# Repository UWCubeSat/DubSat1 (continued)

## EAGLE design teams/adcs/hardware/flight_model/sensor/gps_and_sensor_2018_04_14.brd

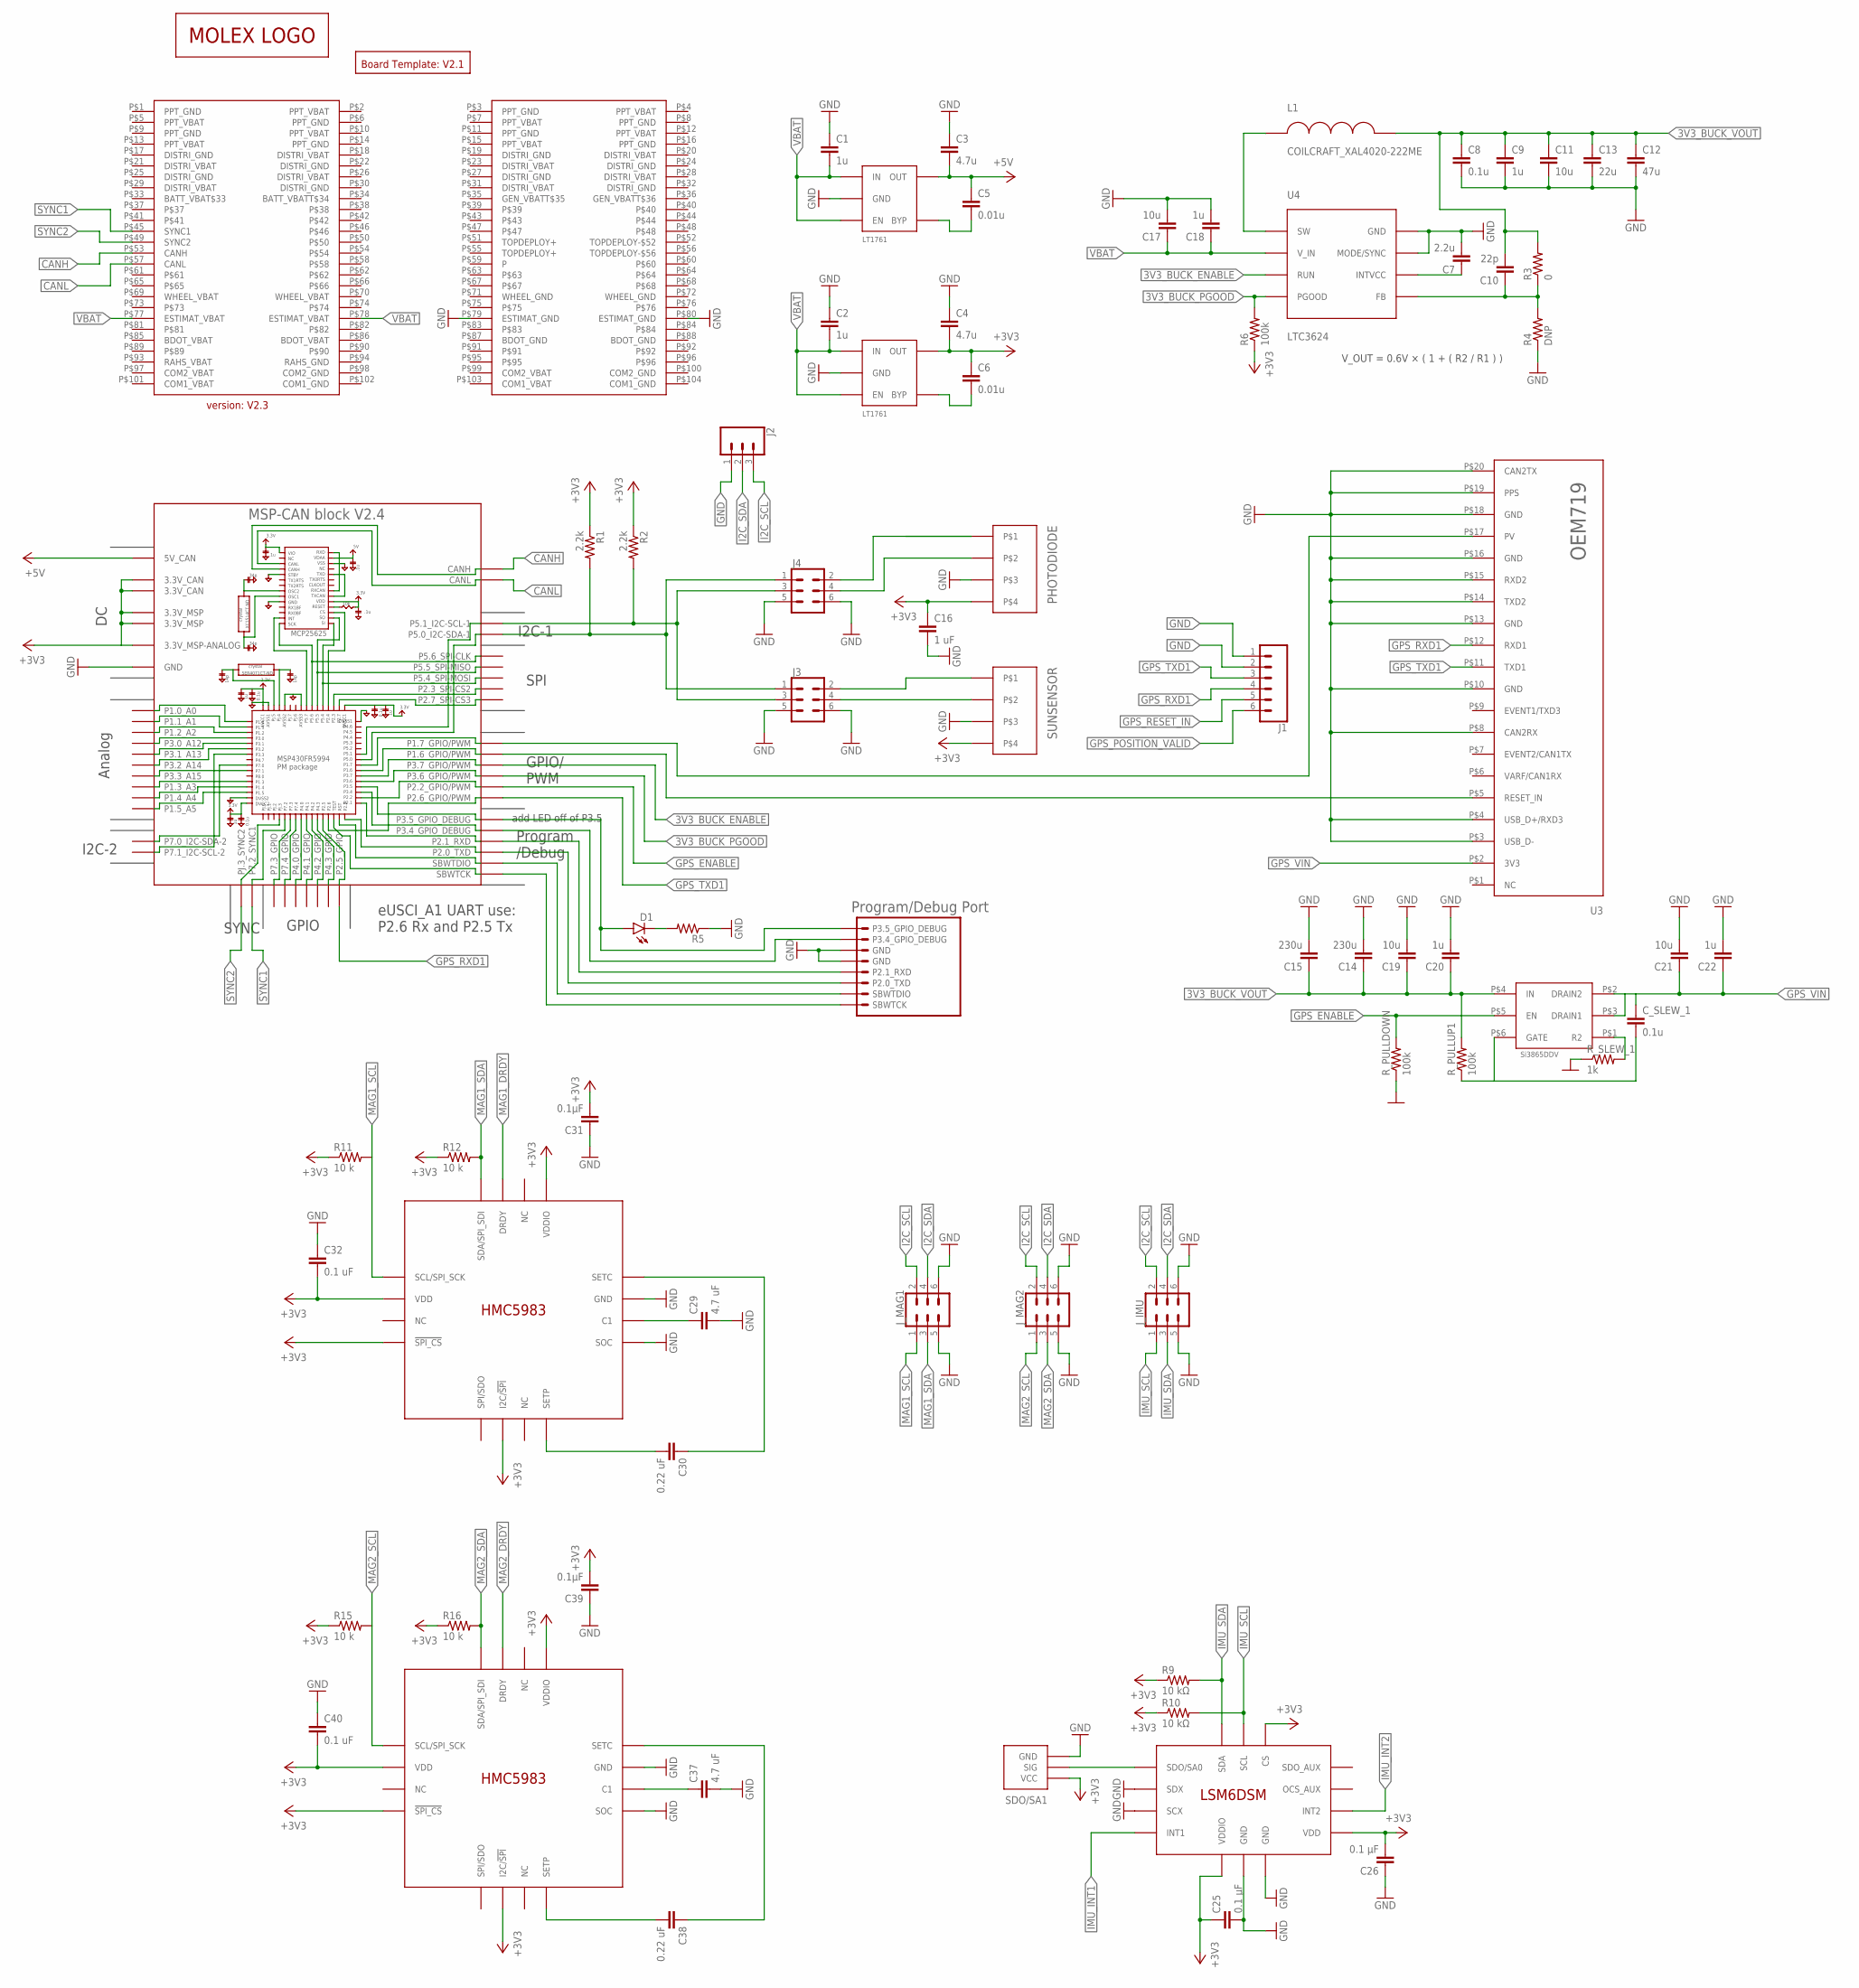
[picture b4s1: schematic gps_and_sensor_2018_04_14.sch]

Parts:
B1: BOARD_TEMPLATESERCURED; BOARD_TEMPLATE_SECURED
BLK1: MSP-CAN_BLOCK
C1, C2, C9, C18, C20, C22: 1u; 0805
C3, C4: 4.7u; 0805
C5, C6: 0.01u; 0805
C7: 2.2u; 0805
C8: 0.1u; 0805
C10: 22p; 0805
C11, C17, C19, C21: 10u; 0805
C12: 47u; 1206
C13: 22u; 1206
C14, C15: 230u; PANASONIC_SVPG
C16: 1 uF; 0805
C25, C26: 0.1 μF; 0805
C29, C37: 4.7 uF; 0805
C30, C38: 0.22 uF; 0805
C31, C39: 0.1µF; 0805
C32, C40: 0.1 uF; 0805
CONN1: PC104_CONNECTOR
C_SLEW_1: 0.1u; 0805
D1: LED; LED-1206
J1: CONN_06LOCK; 1X06_LOCK
J2: CONN_03LOCK; 1X03_LOCK
J3, J4: CONN_03X22X3_SILK_MALE_PTH; 2X3
J_IMU: CONN_03X22X3_SILK_MALE_PTH; 2X3
J_MAG1, J_MAG2: CONN_03X22X3_SILK_MALE_PTH; 2X3
L1: COILCRAFT_XAL4020-222ME; COILCRAFT_XAL4020
PHOTODIODE: PICOLOCK_4
R1, R2: 2.2k; 0805
R3: 0; 0805
R4: DNP; 0805
R5: RESISTOR0805; 0805
R6: 100k; 0805
R9, R10: 10 kΩ; 0805
R11, R12, R15, R16: 10 k; 0805
R_PULLDOWN: 100k; 0805
R_PULLUP1: 100k; 0805
R_SLEW_1: 1k; 0805
SDO/SA1: 0_OHM_JUMPER
SUNSENSOR: PICOLOCK_4
U1, U2: LT1761-X; SOT-23-5
U3: OEM719
U4: LTC3624
U$1: LOGO_MOLEX
U$2: PROGRAM/DEBUG_PORT; 1X08_CONNECTOR
U$3: SI3865DDV; TSOP-6
U$5: LSM6DSM
U$6, U$8: HMC5983

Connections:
3V3_BUCK_ENABLE: BLK1.P3.7_GPIO/PWM, U4.RUN
3V3_BUCK_FB: C10.1, R3.1, R4.2, U4.FB
3V3_BUCK_INTVCC: C7.1, U4.INTVCC
3V3_BUCK_PGOOD: BLK1.P3.6_GPIO/PWM, R6.2, U4.PGOOD
3V3_BUCK_SW: L1.P$1, U4.SW
3V3_BUCK_VOUT: C8.1, C9.1, C10.2, C11.1, C12.1, C13.1, C14.POS (1), C15.POS (1), C19.1, C20.1, L1.P$2, R3.2, R_PULLUP1.2, U$3.P$4 (IN)
+3V3: R6.1
CANH: BLK1.CANH, CONN1.P$53 (CANH)
CANL: BLK1.CANL, CONN1.P$57 (CANL)
GND: BLK1.GND@1 (GND), BLK1.GND@2 (GND), BLK1.GND@3 (GND), BLK1.GND@4 (GND), BLK1.GND@5 (GND), BLK1.GND@7 (GND), BLK1.GND@8 (GND), BLK1.GND@9 (GND), BLK1.GND@10 (GND), BLK1.GND@11 (GND), BLK1.GND@12 (GND), BLK1.GND@13 (GND), BLK1.GND@14 (GND), BLK1.GND@15 (GND), BLK1.GND@16 (GND), BLK1.GND@17 (GND), BLK1.GND@26 (GND), C1.1, C2.1, C3.1, C4.1, C7.2, C8.2, C9.2, C11.2, C12.2, C13.2, C14.NEG (2), C15.NEG (2), C16.2, C17.2, C18.2, C19.2, C20.2, C21.2, C22.2, C25.2, C26.1, C29.2, C31.1, C32.1, C37.2, C39.1, C40.1, CONN1.P$79 (ESTIMAT_GND), CONN1.P$80 (ESTIMAT_GND), J1.1, J1.2, J2.1, J3.5, J3.6, J4.5, J4.6, J_IMU.5, J_IMU.6, J_MAG1.5, J_MAG1.6, J_MAG2.5, J_MAG2.6, PHOTODIODE.P$3, R4.1, R5.1, R_PULLDOWN.1, R_SLEW_1.1, SDO/SA1.P$1 (GND), SUNSENSOR.P$3, U1.P$2 (GND), U2.P$2 (GND), U3.P$3 (USB_D-), U3.P$4 (USB_D+/RXD3), U3.P$8 (CAN2RX), U3.P$10 (GND), U3.P$13 (GND), U3.P$14 (TXD2), U3.P$15 (RXD2), U3.P$16 (GND), U3.P$18 (GND), U3.P$19 (PPS), U3.P$20 (CAN2TX), U4.GND@1 (GND), U4.GND@PAD (GND), U4.MODE/SYNC, U$2.5 (GND), U$2.6 (GND), U$5.GND@1 (GND), U$5.GND@2 (GND), U$5.SCX, U$5.SDX, U$6.GND, U$6.SOC, U$8.GND, U$8.SOC
GPS_ENABLE: BLK1.P2.2_GPIO/PWM, R_PULLDOWN.2, U$3.P$5 (EN)
GPS_POSITION_VALID: BLK1.P1.7_GPIO/PWM, J1.6, U3.P$17 (PV)
GPS_RESET_IN: BLK1.P1.6_GPIO/PWM, J1.5, U3.P$5 (RESET_IN)
GPS_RXD1: BLK1.P2.5_GPIO, J1.4, U3.P$12 (RXD1)
GPS_TXD1: BLK1.P2.6_GPIO/PWM, J1.3, U3.P$11 (TXD1)
GPS_VIN: C21.1, C22.1, C_SLEW_1.1, U3.P$2 (3V3), U$3.P$2 (DRAIN2), U$3.P$3 (DRAIN1)
I2C_SCL: BLK1.P5.1_I2C-SCL-1, J2.3, J3.3, J4.3, J_IMU.2, J_MAG1.2, J_MAG2.2, R2.2
I2C_SDA: BLK1.P5.0_I2C-SDA-1, J2.2, J3.1, J4.1, J_IMU.4, J_MAG1.4, J_MAG2.4, R1.2
IMU_INT1: U$5.INT1
IMU_INT2: U$5.INT2
IMU_SCL: J_IMU.1, R10.2, U$5.SCL
IMU_SDA: J_IMU.3, R9.2, U$5.SDA
LDO_3V3: BLK1.3.3V@CAN1 (3.3V_CAN), BLK1.3.3V@CAN2 (3.3V_CAN), BLK1.3.3V@MSP1 (3.3V_MSP), BLK1.3.3V@MSP2 (3.3V_MSP), BLK1.3.3V_ANALOG@MSP2 (3.3V_MSP-ANALOG), C4.2, C6.1, C16.1, C25.1, C26.2, C31.2, C32.2, C39.2, C40.2, PHOTODIODE.P$4, R1.1, R2.1, R9.1, R10.1, R11.1, R12.1, R15.1, R16.1, SDO/SA1.P$3 (VCC), SUNSENSOR.P$4, U2.P$5 (OUT), U$5.CS, U$5.VDD, U$5.VDDIO, U$6.!SPI_CS, U$6.I2C/!SPI, U$6.VDD, U$6.VDDIO, U$8.!SPI_CS, U$8.I2C/!SPI, U$8.VDD, U$8.VDDIO
LDO_3V3_BYP: C6.2, U2.P$4 (BYP)
LDO_5V: BLK1.5V (5V_CAN), C3.2, C5.1, U1.P$5 (OUT)
LDO_5V_BYP: C5.2, U1.P$4 (BYP)
MA1G_C2: C29.1, U$6.C1
MAG1_DRDY: U$6.DRDY
MAG1_SCL: J_MAG1.1, R11.2, U$6.SCL/SPI_SCK
MAG1_SDA: J_MAG1.3, R12.2, U$6.SDA/SPI_SDI
MAG1_SETC1: C30.1, U$6.SETC
MAG1_SETP1: C30.2, U$6.SETP
MAG2_C1: C37.1, U$8.C1
MAG2_DRDY: U$8.DRDY
MAG2_SCL: J_MAG2.1, R15.2, U$8.SCL/SPI_SCK
MAG2_SDA: J_MAG2.3, R16.2, U$8.SDA/SPI_SDI
MAG2_SETC: C38.1, U$8.SETC
MAG2_SETP: C38.2, U$8.SETP
unnamed: BLK1.P3.5_GPIO_DEBUG, D1.A, U$2.8 (P3.5_GPIO_DEBUG)
unnamed: R_SLEW_1.2, U$3.P$1 (R2)
unnamed: BLK1.P3.4_GPIO_DEBUG, U$2.7 (P3.4_GPIO_DEBUG)
unnamed: C_SLEW_1.2, R_PULLUP1.1, U$3.P$6 (GATE)
unnamed: BLK1.P2.1_RXD, U$2.4 (P2.1_RXD)
unnamed: BLK1.P2.0_TXD, U$2.3 (P2.0_TXD)
unnamed: BLK1.SBWTDIO, U$2.2 (SBWTDIO)
unnamed: BLK1.SBWTCK, U$2.SBWTCK
unnamed: D1.C, R5.2
unnamed: SDO/SA1.P$2 (SIG), U$5.SDO/SA0
PHOTODIODE_SCL: J4.4, PHOTODIODE.P$2
PHOTODIODE_SDA: J4.2, PHOTODIODE.P$1
SUNSENSOR_SCL: J3.4, SUNSENSOR.P$2
SUNSENSOR_SDA: J3.2, SUNSENSOR.P$1
SYNC1: BLK1.P7.2_SYNC1, CONN1.P$45 (SYNC1)
SYNC2: BLK1.PJ.3_SYNC2, CONN1.P$49 (SYNC2)
VBAT: C1.2, C2.2, C17.1, C18.1, CONN1.P$77 (ESTIMAT_VBAT), CONN1.P$78 (ESTIMAT_VBAT), U1.P$1 (IN), U1.P$3 (EN), U2.P$1 (IN), U2.P$3 (EN), U4.V_IN

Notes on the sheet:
V_OUT = 0.6V × ( 1 + ( R2 / R1 ) )

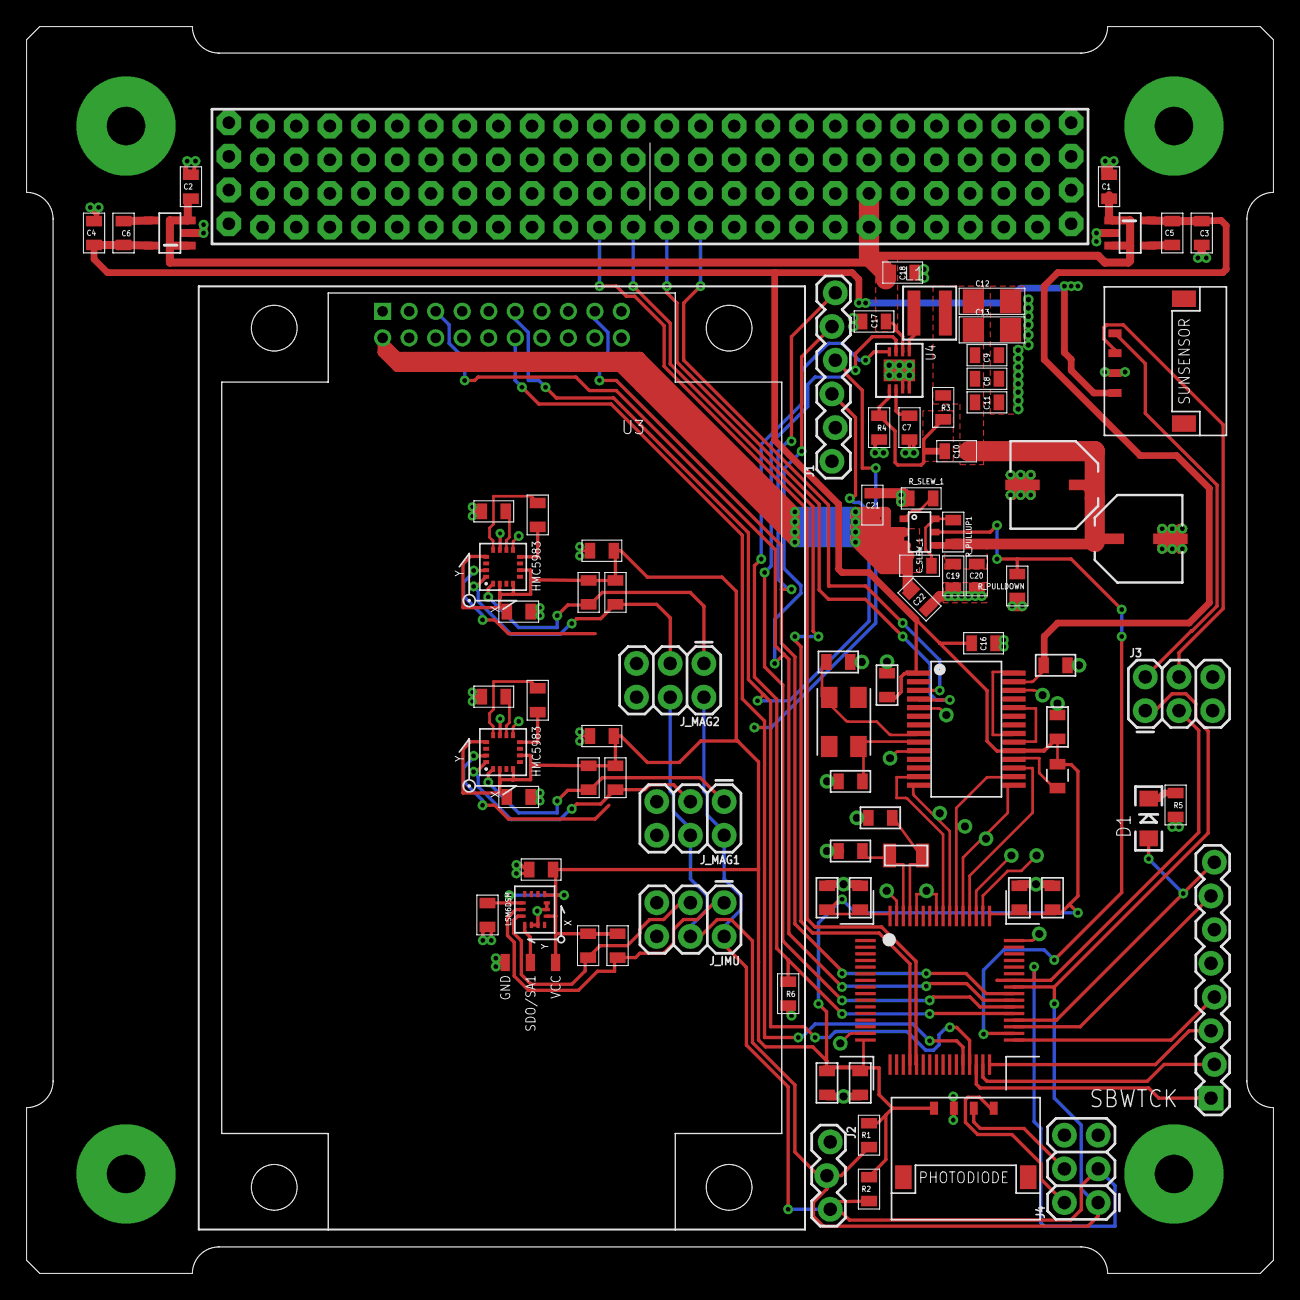
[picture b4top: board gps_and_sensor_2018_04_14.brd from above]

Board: 2 copper layers, 94.0 x 94.0 mm, 73 parts (1 on the bottom side), 50 nets.

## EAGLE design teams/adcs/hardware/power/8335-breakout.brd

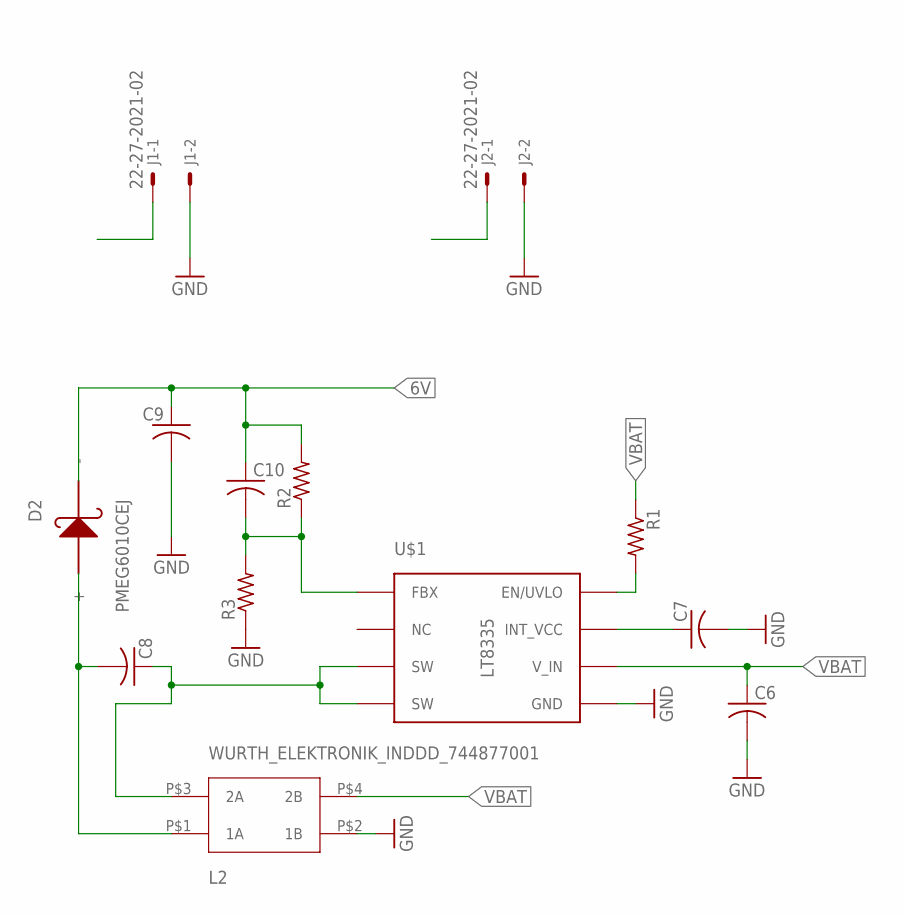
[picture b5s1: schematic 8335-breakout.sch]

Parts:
C6, C7, C8, C9, C10: C-USC0805; C0805
D2: PMEG6010CEJ; SC-90
J1, J2: 22-27-2021-02; 6410-02
L2: WURTH_ELEKTRONIK_INDDD_744877001
R1, R2, R3: R-US_R0805; R0805
U$1: LT8335; DDB

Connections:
6V: C9.1, C10.1, D2.P$2 (-), J1.1, R2.2
EN_UVLO1: R1.2, U$1.P$8 (EN/UVLO)
FBX1: C10.2, R2.1, R3.2, U$1.P$1 (FBX)
GND: C6.2, C7.2, C9.2, J1.2, J2.2, L2.P$2 (1B), R3.1, U$1.GND, U$1.P$5 (GND)
INT_VCC1: C7.1, U$1.P$7 (INT_VCC)
unnamed: C8.2, D2.P$1 (+), L2.P$1 (1A)
SW1: C8.1, L2.P$3 (2A), U$1.P$3 (SW), U$1.P$4 (SW)
VBAT: C6.1, J2.1, L2.P$4 (2B), R1.1, U$1.P$6 (V_IN)

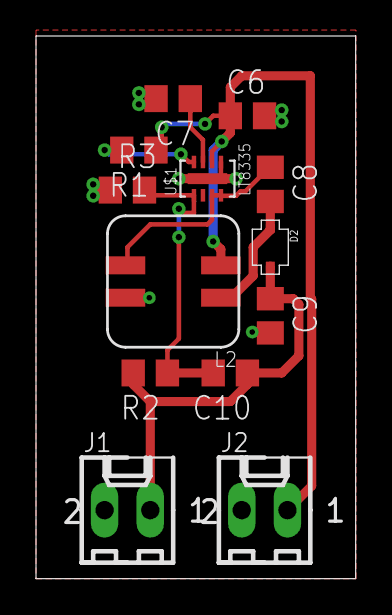
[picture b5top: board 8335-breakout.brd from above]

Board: 2 copper layers, 17.8 x 30.1 mm, 13 parts (0 on the bottom side), 8 nets.
